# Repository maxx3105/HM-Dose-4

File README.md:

# HM-Dose-4
Funk 4-fach Dosierpumpe für die Integration in HomeMatic auf Basis der AskSin++

Dieses Projekt basiert auf der Arbeit von [pa-pa](https://github.com/pa-pa/AskSinPP) ,[Jérôme](https://github.com/jp112sdl/Beispiel_AskSinPP).

# Hardware

### Bauteile

Bauteile                   | Bezeichnung          | Anzahl | Kommentar   | 
-------------------------- | -------------------- | ------ | ----------- | 
R1,R2,R3,R4                | 560 Ohm              |   4    |             |
SR1                        | 1K Ohm               |   1    |  [ELV.de](https://de.elv.com/sicherungswiderstand-1k-091814?fs=1418091890)           |
R5                         | 330 Ohm              |   1    |             |
C1                         | 0,1 µF               |   1    |             |
D1,D2,D3,D4,D5             | 5mm LED Rot          |   5    |             |
SW1                        | Taster               |   1    |             |
PS1                        | MeanWell IRM-30-12   |   1    |             |
X1                         | WAGO 236-403         |   1    |             |
J1                         | DC-DC Wandler        |   1    |             |
U1                         | Arduino MiniPro 3,3V |   1    |             |
U2                         | CC1101               |   1    |             |
U3                         | ULN 2003A            |   1    |             |
RV1                        | Varistor             |   1    |             |

Reichelt Liste https://www.reichelt.de/my/1820811

#### Sonstiges

DC-DC Wandler https://de.aliexpress.com/item/4000938525410.html

CC1101 https://de.aliexpress.com/item/32924239954.html

Dosierpumpen 4 Stk https://de.aliexpress.com/item/32872201122.html

~8,3 cm Draht als Antenne

### Programmieradapter

- 1x FTDI Programmer https://www.az-delivery.de/products/ftdi-adapter-ft232rl

# Software

https://www.arduino.cc/en/software

### Firmware

Sketch https://github.com/pa-pa/AskSinPP/blob/master/examples/HM-LC-SWX-SM/HM-LC-SWX-SM.ino

# Bauanleitung

coming soon

# Bilder

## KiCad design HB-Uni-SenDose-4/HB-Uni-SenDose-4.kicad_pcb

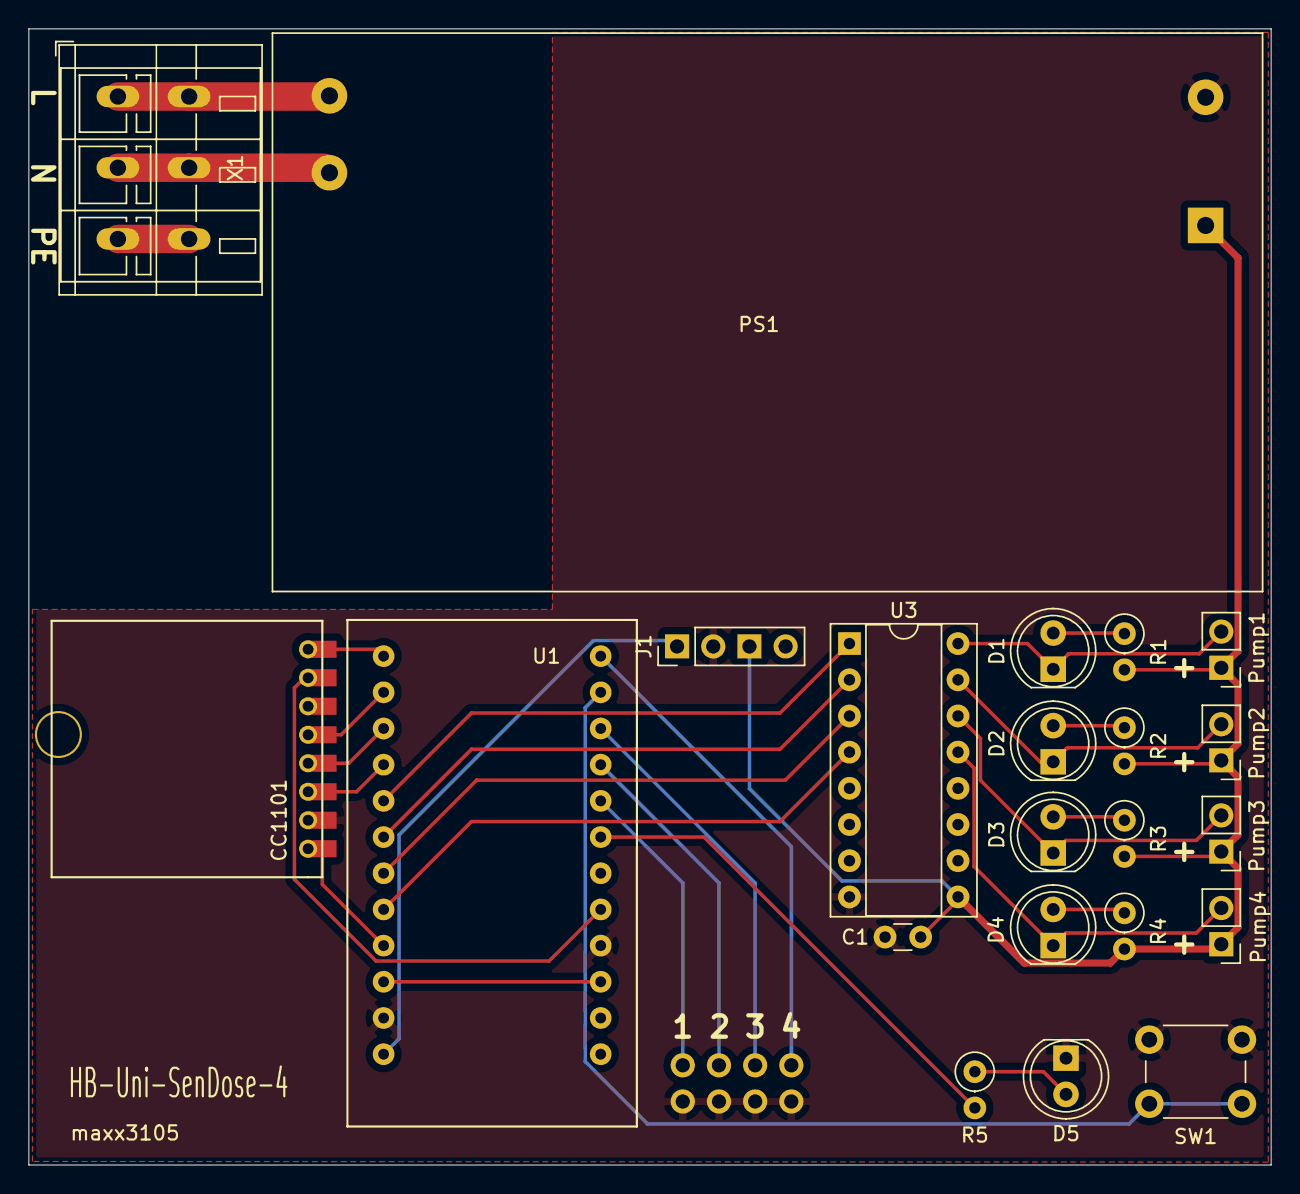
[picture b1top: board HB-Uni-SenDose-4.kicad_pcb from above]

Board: 2 copper layers, 87.2 x 79.8 mm, 23 parts (1 on the bottom side), 30 nets.

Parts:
C1: 0.1uF; C_Disc_D3.0mm_W1.6mm_P2.50mm
D1: LED; LED_D5.0mm
D2: LED1; LED_D5.0mm
D3: LED2; LED_D5.0mm
D4: LED3; LED_D5.0mm
D5: LED4; LED_D5.0mm
J1: DCDC Con; PinHeader_1x04_P2.54mm_Vertical
J6: Switch; PinHeader_2x04_P2.54mm_Vertical
PS1: IRM-60-12; Converter_ACDC_MeanWell_IRM-30-xx_THT
Pump1: Pump1; PinHeader_1x02_P2.54mm_Vertical
Pump2: Pump2; PinHeader_1x02_P2.54mm_Vertical
Pump3: Pump3; PinHeader_1x02_P2.54mm_Vertical
Pump4: Pump4; PinHeader_1x02_P2.54mm_Vertical
R1, R2, R3, R4: 510; R_Axial_DIN0207_L6.3mm_D2.5mm_P2.54mm_Vertical
R5: 330; R_Axial_DIN0207_L6.3mm_D2.5mm_P2.54mm_Vertical
SW1: Config; SW_PUSH_6mm_H4.3mm
U1: Arduino_Pro_Mini; Arduino_Pro_Mini_Outside
U2: CC1101; CC1101_SMD_THT
U3: ULN2003; DIP-16_W7.62mm_Socket
X1: 236-403_334-604; TerminalBlock_WAGO_236-403_1x03_P5.00mm_45Degree

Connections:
/2: U1.2, U2.7
/4: R5.2, U1.4
/5: J6.1, U1.5
/6: J6.3, U1.6
/7: J6.5, U1.7
/8: SW1.1, U1.8
/9: J6.7, U1.9
/10: U1.10, U2.8
/11: U1.11, U2.5
/12: U1.12, U2.4
/13: U1.13, U2.3
/+5V: J1.1, U1.RAW
/+12V: C1.2, J1.3, PS1.1, Pump1.1, Pump2.1, Pump3.1, Pump4.1, R1.2, R2.2, R3.2, R4.2, U3.9
/A0: U1.A0, U3.1
/A1: U1.A1, U3.2
/A2: U1.A2, U3.3
/A3: U1.A3, U3.4
/Pump1: D1.1, Pump1.2, U3.16
/Pump2: D2.1, Pump2.2, U3.15
/Pump3: D3.1, Pump3.2, U3.14
/Pump4: D4.1, Pump4.2, U3.13
/VCC: U1.VCC, U2.1
GND: C1.1, D5.1, J1.2, J6.2, J6.4, J6.6, J6.8, PS1.2, SW1.2, U1.GND, U2.2, U3.8
unnamed: D1.2, R1.1
unnamed: D2.2, R2.1
unnamed: D3.2, R3.1
unnamed: D4.2, R4.1
unnamed: D5.2, R5.1
unnamed: PS1.4, X1.1
unnamed: PS1.3, X1.2

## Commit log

2021-03-16 Update README.md
    Some Changes
2021-03-17 Add files via upload
    Bugfix
